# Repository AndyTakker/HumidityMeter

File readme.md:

Напиши сюда краткое описание проекта

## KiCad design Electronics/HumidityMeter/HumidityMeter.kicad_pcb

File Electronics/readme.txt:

В этом каталоге находятся электрические схемы и разводка плат

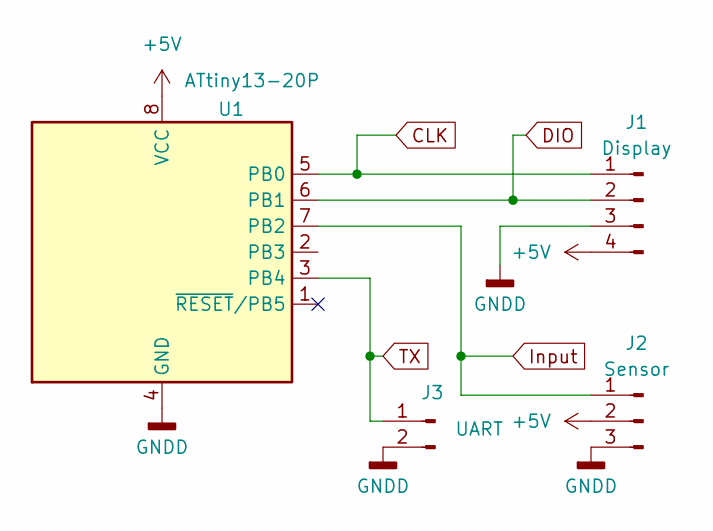
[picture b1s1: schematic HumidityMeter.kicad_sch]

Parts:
J1: Display; PinSocket_1x04_P2.54mm_Vertical
J2: Sensor; PinHeader_1x03_P2.54mm_Vertical
J3: UART; PinSocket_1x02_P2.54mm_Vertical
U1: ATtiny13-20P; DIP-8_W7.62mm

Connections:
+5V: J1.4, J2.2, U1.8 (VCC)
CLK: J1.1, U1.5 (PB0)
DIO: J1.2, U1.6 (PB1)
GNDD: J1.3, J2.3, J3.2, U1.4 (GND)
Input: J2.1, U1.7 (PB2)
TX: J3.1, U1.3 (PB4)

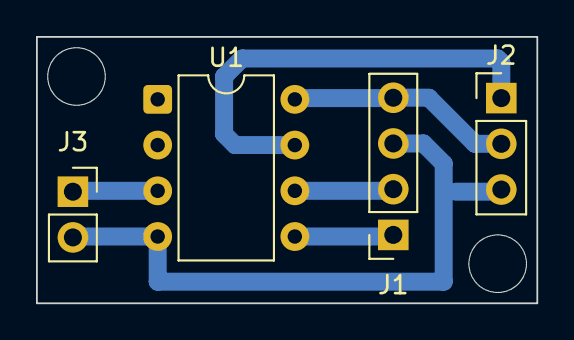
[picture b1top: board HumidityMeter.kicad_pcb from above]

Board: 2 copper layers, 27.8 x 14.8 mm, 4 parts (0 on the bottom side), 6 nets.

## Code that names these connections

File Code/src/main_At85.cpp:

//============================================================= (c) A.Kolesov ==
// Измерение влажности почвы с помощью аналогового датчика HW-390
// Поскольку точность датчика - лаптем по карте, цифровая индикация смысла не имеет
// Будем отображать светодиодами три уровня: низкий/в норме/высокий.
// Техническая реализация:
// - делаем на Attiny85, отлаживаемся и калибруем через SoftwareSerial и прошиваем
//   через сервисный интерфейс Arduino IDE
// - затем все переносим  на Attiny13
//
// Напоминалка, как работать с Digispark + Micronucleus
//  1. Компилируем и загружаем код в VSCode+PlatformIO
//  2. В момент загузки, по подсказке VSCode, подключаем Digispark к USB
//  3. После прошивки отключаем от USB.
//  4. Подключаем конвертор USB-UART к пинам Digispark (RX/TX SoftwareSerial)
//  5. Отлаживаемся через Serial Monitor и print(). Одновременно USB и конвертор
//     не работают.
//  6. Итоговую прошивку записываем в контроллер програматором.
// Если используется LED_DISPLAY_ENABLED, на момент прошивки его надо отключать.
// Светодиоды на шинах дисплея не мешают дисплею.
//
// Для большинства растений в обычном грунте актуальны следующие значения:
// 0% – 15%:    Критически сухо. Почва пылеобразная, растения в стадии завядания. Срочный полив.
// 15% – 30%:   Сухо. Почва рассыпается, не держит форму. Подходит только для кактусов и суккулентов.
// 30% – 60%:   Оптимально (зона комфорта). Почва влажная на ощупь, легко лепится в комок. Идеально для большинства комнатных растений и овощей.
// 60% – 85%:   Очень влажно. Почва мажется, комок при нажатии выделяет влагу. Подходит для влаголюбивых культур (например, огурцы или капуста в период роста).
// 85% – 100%:  Переувлажнение (болото). Корни могут начать гнить из-за нехватки кислорода.
//
// Рекомендации для конкретных групп растений:
// Суккуленты	      15% – 25%	Алоэ, кактусы, толстянка
// Декоративные	    35% – 50%	Фикусы, монстера, пальмы
// Овощные культуры 45% – 70%	Томаты, перец, зелень
// Влаголюбивые	    60% – 85%	Огурцы, циперус, папоротники
//------------------------------------------------------------------------------
#include <Arduino.h>
#ifndef ATtiny13
#include <Soft_Serial.h>
#endif
#ifdef LED_DISPLAY_ENABLED
#include <TM1637Display.h>
#endif

// Конфигурируем железо
#define pinRx PB0     // Вывод RX для serial (не используется)
#define pinTx PB1     // Вывод TX для serial
#define pinSensor PB2 // Вход датчика влажности
#ifdef ATtiny13
#define ADC_NUM A1 // Номер аналогового входа на PB2
#else
#define ADC_NUM 1 // Номер аналогового входа на PB2
#endif

#ifdef LED_DISPLAY_ENABLED
#define CLK PB3
#define DIO PB4
#else
#define pinLedLow PB3  // Светодиод низкого уровня влажности
#define pinLedHigh PB4 // Светодиод высокого уровня влажности
#endif

// Зададим пороговые значения влажности
#define RAW_SENSOR_100 190 // Абсолютные показания датчика влажности при 100% (в воде)
#define RAW_SENSOR_0 465   // Абсолютные показания датчика влажности при 0% (в воздухе)
#define HUMIDITY_LOW 30    // Нижняя граница влажности (%)
#define HUMIDITY_HIGH 65   // Верхняя граница влажности (%)

#define SCAN_PERIOD 500 // Период сканирования датчика (ms)

// Управление светодиодными индикаторам верхней и нижней границы
#define LOW_ON() digitalWrite(pinLedLow, HIGH)
#define LOW_OFF() digitalWrite(pinLedLow, LOW)
#define HIGH_ON() digitalWrite(pinLedHigh, HIGH)
#define HIGH_OFF() digitalWrite(pinLedHigh, LOW)

#ifndef ATtiny13
// Создадим последовательный порт, через который будем работать
SoftwareSerial softSerial(pinRx, pinTx);
#endif

#ifdef LED_DISPLAY_ENABLED
TM1637Display display(CLK, DIO);
#endif

void printLog(uint16_t hm) {
#ifndef ATtiny13
  char str[10];
  sprintf(str, "Humidity: %d%%\r\n", hm);
  softSerial.print(str);
#endif

#ifdef LED_DISPLAY_ENABLED
  display.showNumberDec(hm, false, 4, 0);
#endif
}

//------------------------------------------------------------------------------
void setup() {
#ifndef ATtiny13
  softSerial.begin(9600);
#endif

  // pinMode(pinSensor, INPUT);

#ifdef LED_DISPLAY_ENABLED
  // display.setBrightness(0x0f);
#else
  pinMode(pinLedLow, OUTPUT);
  pinMode(pinLedHigh, OUTPUT);

  for (int i = 0; i < 3; i++) { // Помигаем как признак жизни
    LOW_ON();
    delay(500);
    LOW_OFF();
    HIGH_ON();
    delay(500);
    HIGH_OFF();
  }
  LOW_OFF();
  HIGH_OFF();
#endif
}

//==============================================================================
// Каждые N миллисекунд читаем показания датчика влажности и выводим
// уровень светодиодами.
//------------------------------------------------------------------------------
void loop() {
  uint16_t hm = 0;                                    // Значение влажности
  hm = analogRead(ADC_NUM);                           // Абсолютные показания датчика
  hm = constrain(hm, (uint16_t)RAW_SENSOR_100, (uint16_t)RAW_SENSOR_0);   // Ограничим возможные всплески выхода за диапазон
  hm = map(hm, RAW_SENSOR_0, RAW_SENSOR_100, 0, 100); // Конвертируем в %
  printLog(hm);

#ifndef LED_DISPLAY_ENABLED
  // Покажем светодиодами уровень влажности
  if (hm < HUMIDITY_LOW) { // Влажность ниже нормы
    LOW_ON();
    HIGH_OFF();
  } else if (hm > HUMIDITY_HIGH) { // Влажность выше нормы
    LOW_OFF();
    HIGH_ON();
  } else { // Влажность в норме
    LOW_ON();
    HIGH_ON();
  }
#endif

  delay(SCAN_PERIOD);
}

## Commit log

2026-03-03 Initial - измертель влажности почвы в вариантах для CH32 и AVR с индикацией порогов светодиодами и с дисплеем.
2026-03-03 Отключение букв в знакогенераторе
2026-03-15 Для ATtiny13 компактный вариант от Qwen (еще не проверен)
2026-03-15 Рабочая версия для двух контроллеров и с выводом на дисплей.
2026-03-15 Удалил неработающие варианты Qwen-а. Они компактные, но не работают.
2026-03-16 Добавлена схема и печатная плата
2026-03-17 Прошита ATtiny13, все ok
